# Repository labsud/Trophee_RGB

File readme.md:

Sujet forum : http://forum.labsud.org/viewtopic.php?f=45&t=191

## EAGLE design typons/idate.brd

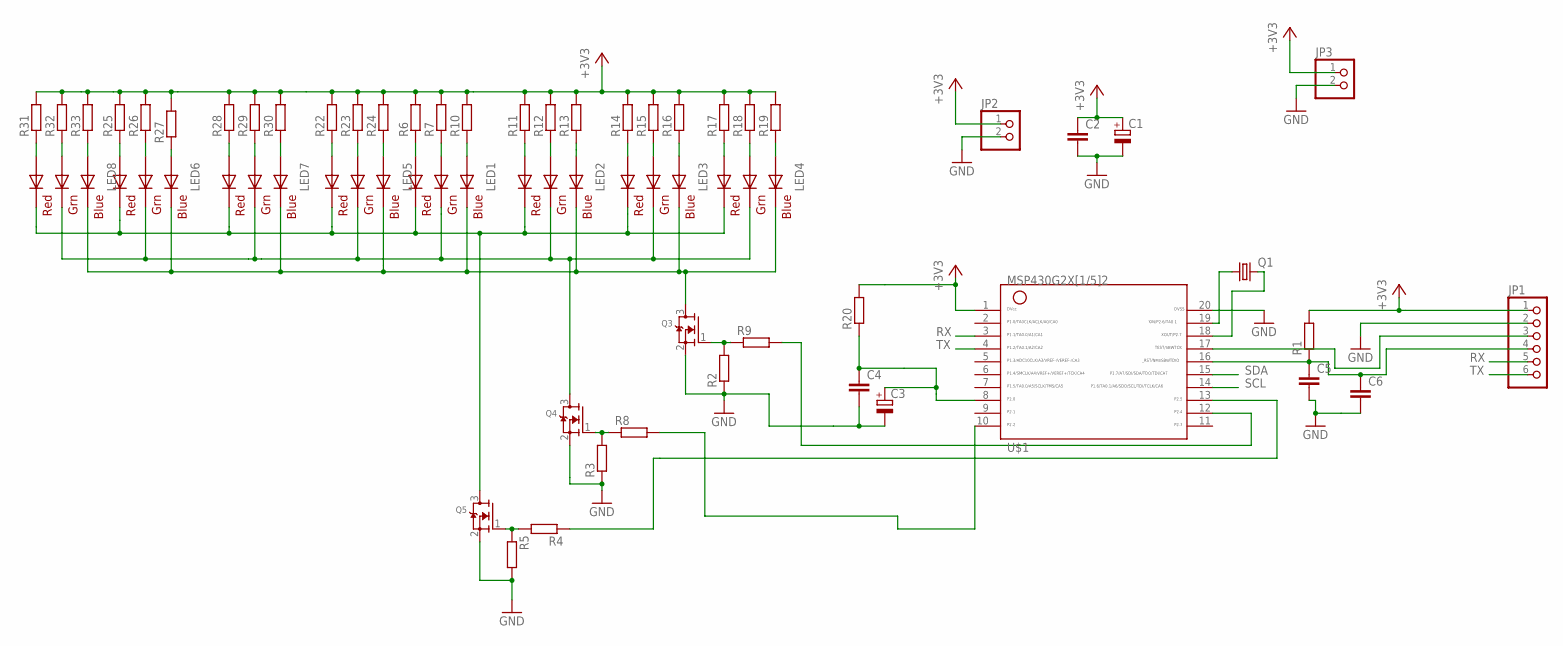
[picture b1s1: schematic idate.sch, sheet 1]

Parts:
C1: CPOL-EUE5-8.5; E5-8,5
C2: C-EU025-030X050; C025-030X050
C3: CPOL-EUTT2D6L; TT2D6L
C4, C6: C-EUC0603; C0603
C5: C-EU050-024X044; C050-024X044
JP1: HEADER-1X6; 1X06_OVAL
JP2, JP3: HEADER-1X2; 1X02_OVAL
LED1, LED2, LED3, LED4, LED5, LED6, LED7, LED8: RGBLED5050
Q1: CRYSTALTC26H; TC26H
Q3, Q4, Q5: MOSFET-NREFLOW; SOT23
R1, R2, R3, R4, R5, R6, R7, R8, R9, R10, R11, R12, R13, R14, R15, R16, R17, R18, R19, R20, R22, R23, R24, R25, R26, R27, R28, R29, R30, R31, R32, R33: R-EU_0204/7; 0204/7
U$1: G2X[1/5]2---N20; N20

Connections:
+3V3: C1.+, C2.1, JP1.1, JP2.1, JP3.1, R1.2, R6.2, R7.2, R10.2, R11.2, R12.2, R13.2, R14.2, R15.2, R16.2, R17.2, R18.2, R19.2, R20.2, R22.2, R23.2, R24.2, R25.2, R26.2, R27.2, R28.2, R29.2, R30.2, R31.2, R32.2, R33.2, U$1.1
BLUE: LED1.6 (GREEN_C), LED2.6 (GREEN_C), LED3.6 (GREEN_C), LED4.6 (GREEN_C), LED5.6 (GREEN_C), LED6.6 (GREEN_C), LED7.6 (GREEN_C), LED8.6 (GREEN_C), Q4.3 (D)
GND: C1.-, C2.2, C3.-, C4.2, C5.2, C6.2, JP1.2, JP2.2, JP3.2, Q3.2 (S), Q4.2 (S), Q5.2 (S), R2.1, R3.1, R5.2, U$1.20
unnamed: JP1.3, U$1.17
unnamed: Q5.1 (G), R4.2, R5.1
unnamed: Q1.1, U$1.19
unnamed: Q4.1 (G), R3.2, R8.1
unnamed: R8.2, U$1.10
unnamed: R4.1, U$1.13
unnamed: C5.1, C6.1, JP1.4, R1.1, U$1.16
unnamed: R9.2, U$1.12
unnamed: Q3.1 (G), R2.2, R9.1
unnamed: Q1.2, U$1.18
unnamed: LED1.2 (RED_A), R6.1
unnamed: LED1.1 (GREEN_A), R7.1
unnamed: LED1.3 (BLUE_A), R10.1
unnamed: LED2.2 (RED_A), R11.1
unnamed: LED2.1 (GREEN_A), R12.1
unnamed: LED2.3 (BLUE_A), R13.1
unnamed: LED3.2 (RED_A), R14.1
unnamed: LED3.1 (GREEN_A), R15.1
unnamed: LED3.3 (BLUE_A), R16.1
unnamed: LED4.2 (RED_A), R17.1
unnamed: LED4.1 (GREEN_A), R18.1
unnamed: LED4.3 (BLUE_A), R19.1
unnamed: LED5.3 (BLUE_A), R24.1
unnamed: LED6.3 (BLUE_A), R27.1
unnamed: LED7.2 (RED_A), R28.1
unnamed: LED7.1 (GREEN_A), R29.1
unnamed: C3.+, C4.1, R20.1, U$1.8
unnamed: LED7.3 (BLUE_A), R30.1
unnamed: LED8.2 (RED_A), R31.1
unnamed: LED8.1 (GREEN_A), R32.1
unnamed: LED8.3 (BLUE_A), R33.1
unnamed: LED1.4 (BLUE_C), LED2.4 (BLUE_C), LED3.4 (BLUE_C), LED4.4 (BLUE_C), LED5.4 (BLUE_C), LED6.4 (BLUE_C), LED7.4 (BLUE_C), LED8.4 (BLUE_C), Q3.3 (D)
unnamed: LED5.2 (RED_A), R22.1
unnamed: LED5.1 (GREEN_A), R23.1
unnamed: LED6.2 (RED_A), R25.1
unnamed: LED6.1 (GREEN_A), R26.1
RED: LED1.5 (RED_C), LED2.5 (RED_C), LED3.5 (RED_C), LED4.5 (RED_C), LED5.5 (RED_C), LED6.5 (RED_C), LED7.5 (RED_C), LED8.5 (RED_C), Q5.3 (D)
RX: JP1.5, U$1.3
SCL: U$1.14
SDA: U$1.15
TX: JP1.6, U$1.4

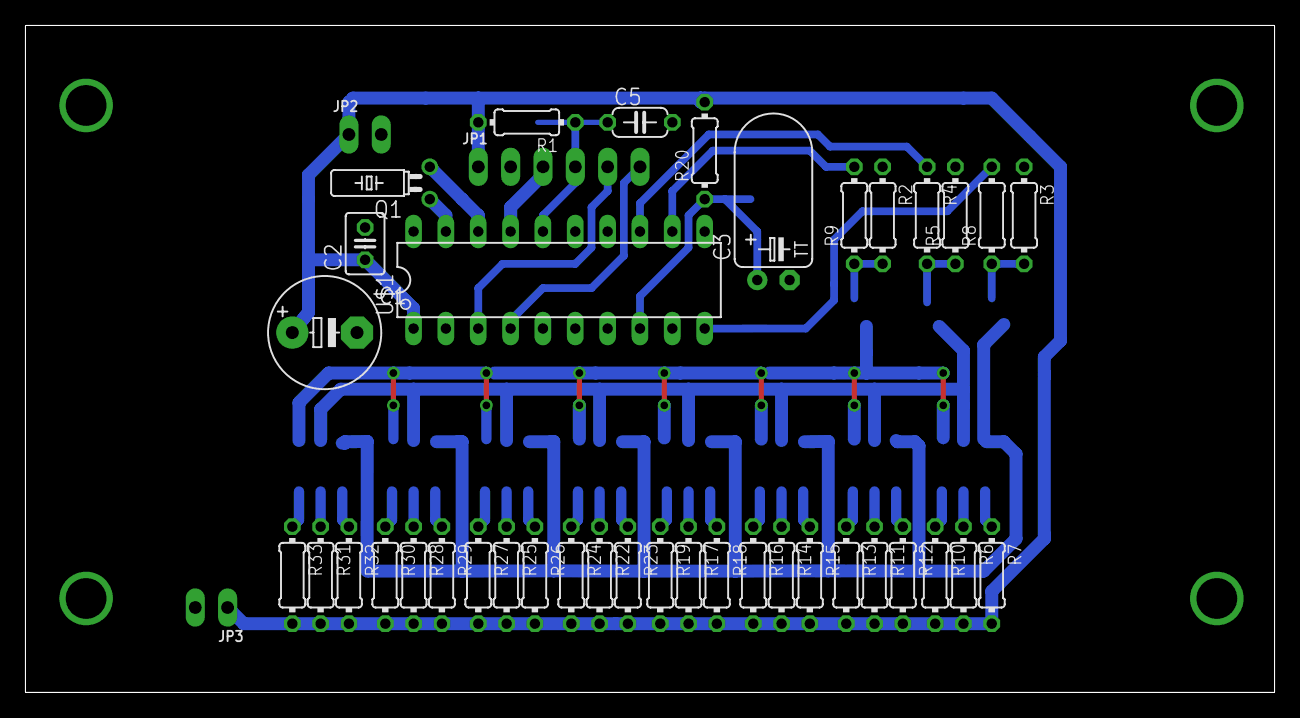
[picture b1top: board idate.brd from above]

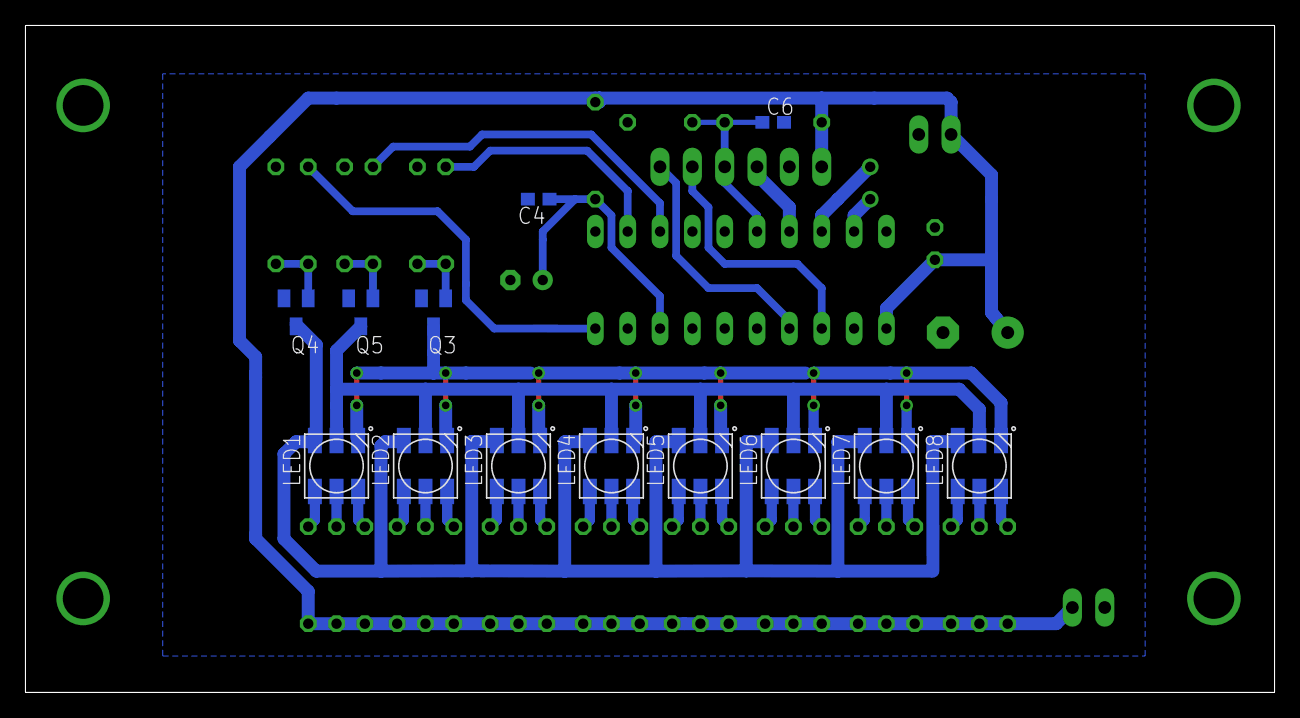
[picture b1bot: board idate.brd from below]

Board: 2 copper layers, 98.1 x 52.4 mm, 54 parts (13 on the bottom side), 42 nets.

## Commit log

2016-01-19 :circus_tent: Added .gitattributes & .gitignore files
2016-01-19 Initial realease
2016-01-19 Inital release
2016-01-19 Initial release

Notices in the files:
parts and their libraries:
microbuilder: This work is placed in the public domain, and may be freely used for commercial and non-commercial work with the following conditions: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
